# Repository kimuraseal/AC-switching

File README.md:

# 4CH AC, 2CH DC Switching and ZCD
The circuit consist of 
- Four optoisolated TRIAC switching circuit.
  Two channels being zero cross switched and other two being random phase switched.
- Two optoisolated MOSFET switching circuit.
  Capable of High speed operations.
- Zero Cross Detector.

# 4CH AC、2CH DC スイッチングおよびZCD
この回路は以下の構成になっています。
- 光アイソレーション付きTRIACスイッチング回路（4系統）
  2つはゼロクロススイッチング
  2つはランダムフェーズスイッチング
- 光アイソレーション付きMOSFETスイッチング回路（2系統）
  高速動作が可能
- ゼロクロス検出回路

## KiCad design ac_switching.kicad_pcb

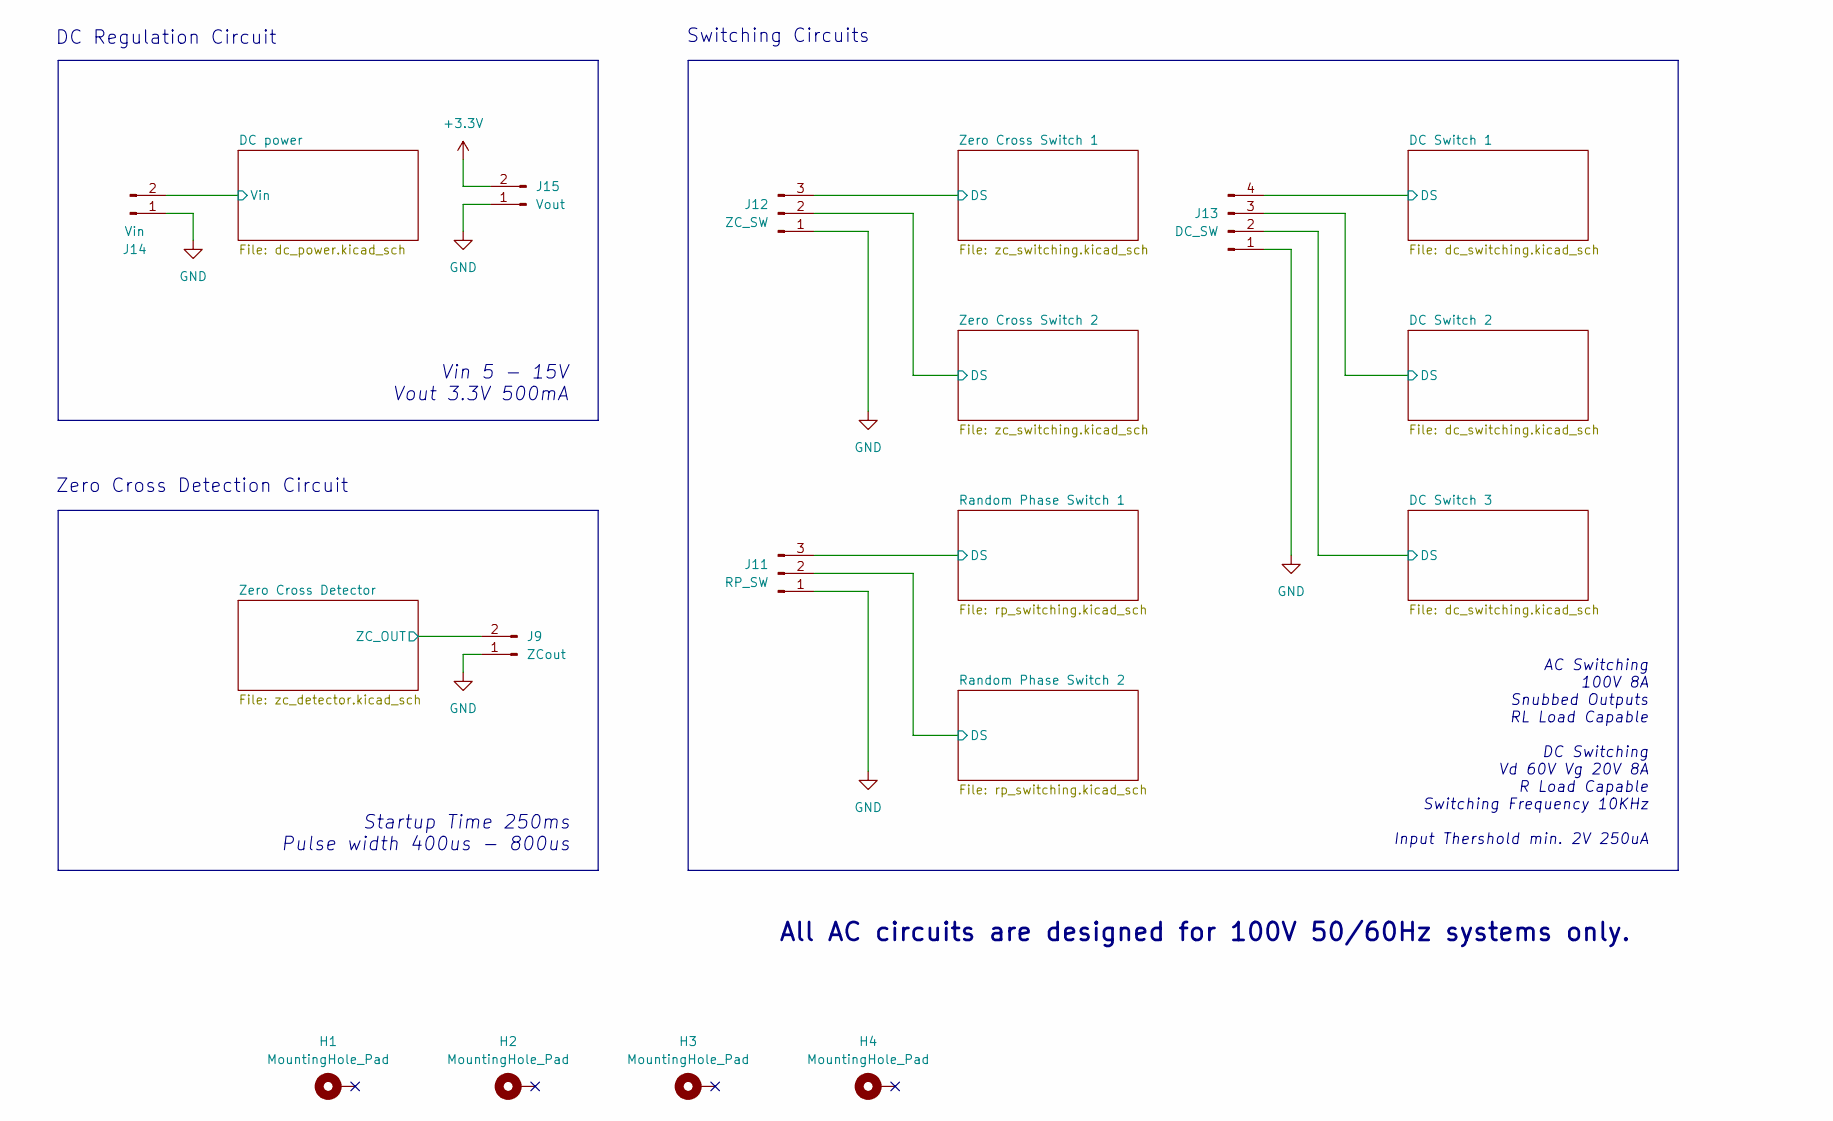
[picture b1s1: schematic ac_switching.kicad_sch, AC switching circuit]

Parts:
H1, H2, H3, H4: MountingHole_Pad; 3mm Mouting hole
J9: ZCout; PinSocket_1x02_P2.54mm_Vertical
J11: RP_SW; PinSocket_1x03_P2.54mm_Vertical
J12: ZC_SW; PinSocket_1x03_P2.54mm_Vertical
J13: DC_SW; PinSocket_1x04_P2.54mm_Vertical
J14: Vin; PinSocket_1x02_P2.54mm_Vertical
J15: Vout; PinSocket_1x02_P2.54mm_Vertical

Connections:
+3.3V: J15.2; also elsewhere on the board
/DC Switch 1/DS: J13.4; also elsewhere on the board
/DC Switch 2/DS: J13.3; also elsewhere on the board
/DC Switch 3/DS: J13.2; also elsewhere on the board
/DC power/Vin: J14.2; also elsewhere on the board
/Random Phase Switch 1/DS: J11.3; also elsewhere on the board
/Random Phase Switch 2/DS: J11.2; also elsewhere on the board
/Zero Cross Detector/ZC_OUT: J9.2; also elsewhere on the board
/Zero Cross Switch 1/DS: J12.3; also elsewhere on the board
/Zero Cross Switch 2/DS: J12.2; also elsewhere on the board
GND: J9.1, J11.1, J12.1, J13.1, J14.1, J15.1; also elsewhere on the board

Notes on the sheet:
Startup Time 250ms Pulse width 400us - 800us
Vin 5 - 15V Vout 3.3V 500mA
DC Regulation Circuit
AC Switching 100V 8A Snubbed Outputs RL Load Capable DC Switching Vd 60V Vg 20V 8A R Load Capable Switching Frequency 10KHz Input Thershold min. 2V 250uA
All AC circuits are designed for 100V 50/60Hz systems only.
Switching Circuits
Zero Cross Detection Circuit

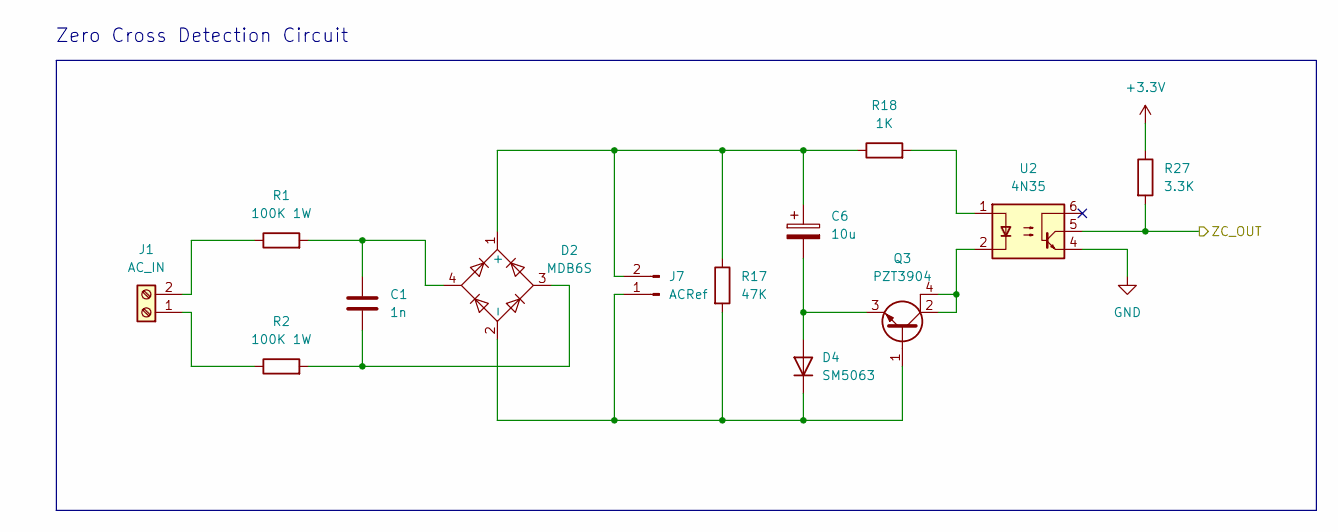
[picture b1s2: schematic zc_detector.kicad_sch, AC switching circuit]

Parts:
C1: 1n; TDK B32529C6102
C6: 10u; Rubycon YXF 50V 10uF
D2: MDB6S; TSSOP-4_4.4x5mm_P4mm
D4: SM5063; D_MELF
J1: AC_IN; TerminalBlock_bornier-2_P5.08mm
J7: ACRef; PinSocket_1x02_P2.54mm_Vertical
Q3: PZT3904; SOT-223
R1, R2: 100K 1W; Yageo RC_L 1218
R17: 47K; Yageo RC_L 1206
R18: 1K; Yageo RC_L 1206
R27: 3.3K; Yageo RC_L 1206
U2: 4N35; DIP-6_W7.62mm

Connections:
+3.3V: R27.1; also elsewhere on the board
/Zero Cross Detector/ZC_OUT: R27.2, U2.5; also elsewhere on the board
GND: U2.4; also elsewhere on the board
unnamed: C1.1, D2.4, R1.2
unnamed: C1.2, D2.3, R2.2
unnamed: C6.1, D2.1 (+), J7.2, R17.1, R18.1
unnamed: D2.2 (-), D4.1 (K), J7.1, Q3.1 (B), R17.2
unnamed: C6.2, D4.2 (A), Q3.3 (E)
unnamed: J1.1, R2.1
unnamed: J1.2, R1.1
unnamed: Q3.2 (C), Q3.4 (C), U2.2
unnamed: R18.2, U2.1

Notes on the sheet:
Zero Cross Detection Circuit

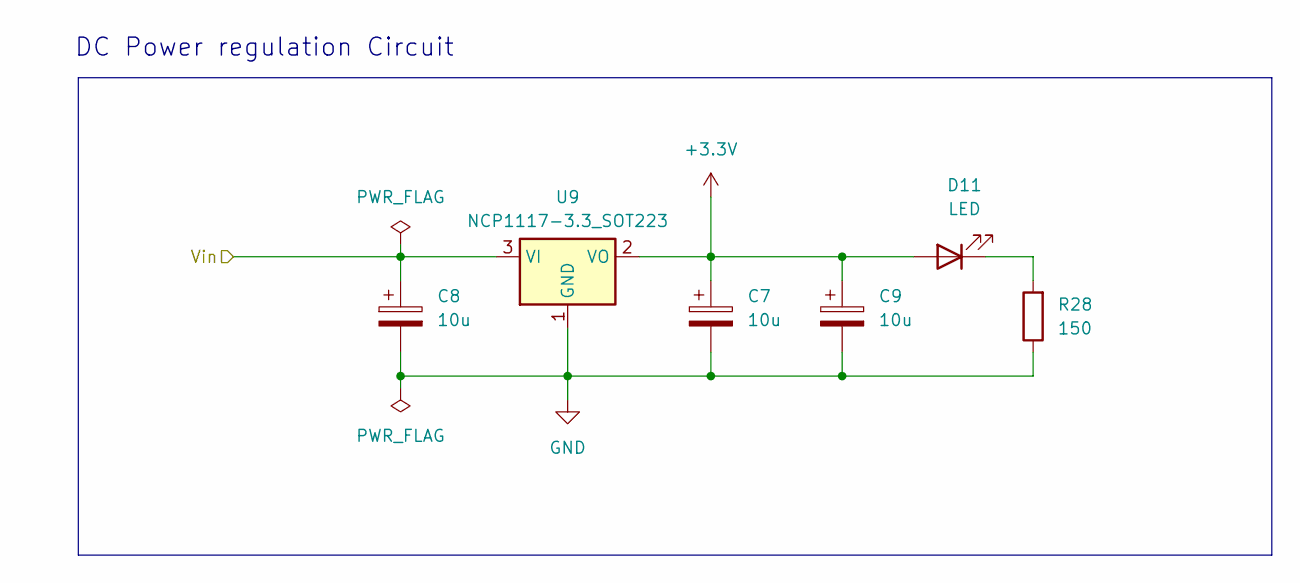
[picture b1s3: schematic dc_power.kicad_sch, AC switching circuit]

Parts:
C7, C8, C9: 10u; Rubycon YXF 50V 10uF
D11: LED; Lite On LTST-C150
R28: 150; Yageo RC_L 1206
U9: NCP1117-3.3_SOT223; SOT-223-3_TabPin2

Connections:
+3.3V: C7.1, C9.1, D11.2 (A), U9.2 (VO); also elsewhere on the board
/DC power/Vin: C8.1, U9.3 (VI); also elsewhere on the board
GND: C7.2, C8.2, C9.2, R28.1, U9.1 (GND); also elsewhere on the board
unnamed: D11.1 (K), R28.2

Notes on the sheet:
DC Power regulation Circuit

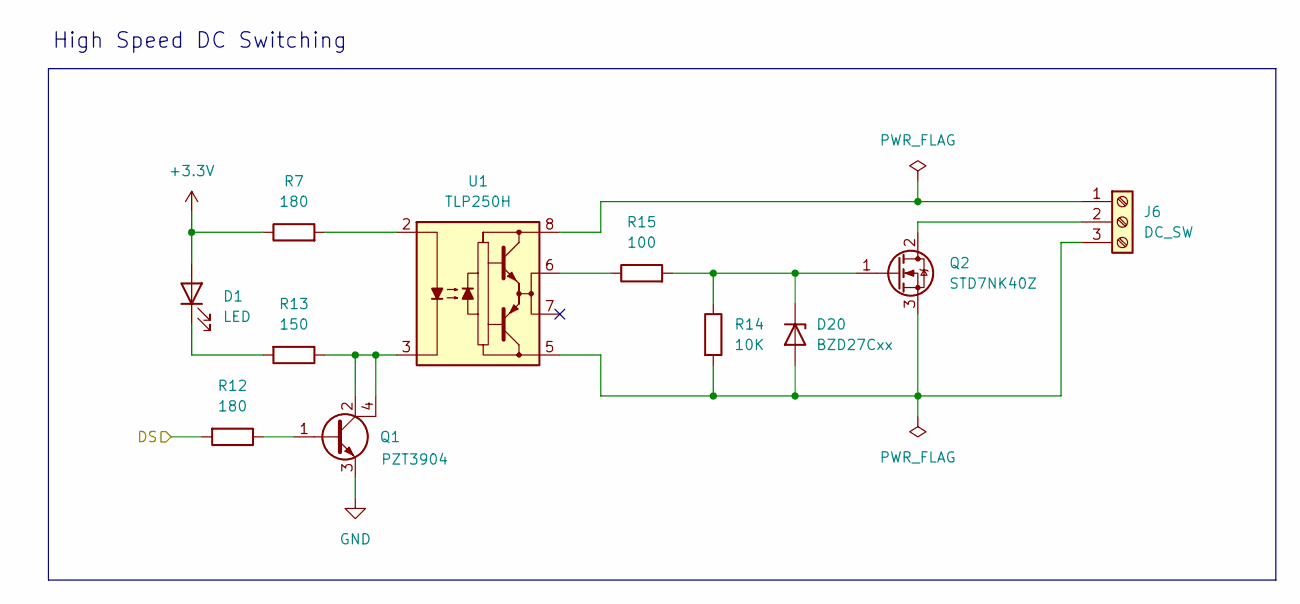
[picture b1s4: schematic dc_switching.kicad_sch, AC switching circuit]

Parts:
D1: LED; Lite On LTST-C150
D20: BZD27Cxx; D_SMF
J6: DC_SW; TerminalBlock_bornier-3_P5.08mm
Q1: PZT3904; SOT-223
Q2: STD7NK40Z; TO-252-2
R7, R12: 180; Yageo RC_L 1206
R13: 150; Yageo RC_L 1206
R14: 10K; Yageo RC_L 1206
R15: 100; Yageo RC_L 1206
U1: TLP250H; DIP-8_W7.62mm

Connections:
+3.3V: D1.2 (A), R7.1; also elsewhere on the board
/DC Switch 1/DS: R12.2; also elsewhere on the board
GND: Q1.3 (E); also elsewhere on the board
unnamed: D1.1 (K), R13.2
unnamed: D20.2 (A), J6.3, Q2.3 (S), R14.2, U1.5 (VEE)
unnamed: D20.1 (K), Q2.1 (G), R14.1, R15.2
unnamed: J6.1, U1.8 (VCC)
unnamed: J6.2, Q2.2 (D)
unnamed: Q1.1 (B), R12.1
unnamed: R15.1, U1.6 (VO)
unnamed: R7.2, U1.2 (A)
unnamed: Q1.2 (C), Q1.4 (C), R13.1, U1.3 (C)

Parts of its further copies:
D8, D16: LED; Lite On LTST-C150
D21, D22: BZD27Cxx; D_SMF
J8, J10: DC_SW; TerminalBlock_bornier-3_P5.08mm
Q4, Q10: PZT3904; SOT-223
Q5, Q11: STD7NK40Z; TO-252-2
R16, R23, R41, R45: 180; Yageo RC_L 1206
R24, R42: 150; Yageo RC_L 1206
R25, R44: 100; Yageo RC_L 1206
R26, R43: 10K; Yageo RC_L 1206
U3, U8: TLP250H; DIP-8_W7.62mm

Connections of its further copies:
+3.3V: D8.2 (A), D16.2 (A), R16.1, R45.1; also elsewhere on the board
/DC Switch 2/DS: R23.2; also elsewhere on the board
/DC Switch 3/DS: R41.2; also elsewhere on the board
GND: Q4.3 (E), Q10.3 (E); also elsewhere on the board
unnamed: D8.1 (K), R24.2
unnamed: D16.1 (K), R42.2
unnamed: D21.2 (A), J8.3, Q5.3 (S), R26.2, U3.5 (VEE)
unnamed: D21.1 (K), Q5.1 (G), R25.2, R26.1
unnamed: D22.2 (A), J10.3, Q11.3 (S), R43.2, U8.5 (VEE)
unnamed: D22.1 (K), Q11.1 (G), R43.1, R44.2
unnamed: J8.1, U3.8 (VCC)
unnamed: J8.2, Q5.2 (D)
unnamed: J10.1, U8.8 (VCC)
unnamed: J10.2, Q11.2 (D)
unnamed: Q4.1 (B), R23.1
unnamed: Q10.1 (B), R41.1
unnamed: R25.1, U3.6 (VO)
unnamed: R44.1, U8.6 (VO)
unnamed: R16.2, U3.2 (A)
unnamed: Q4.2 (C), Q4.4 (C), R24.1, U3.3 (C)
unnamed: R45.2, U8.2 (A)
unnamed: Q10.2 (C), Q10.4 (C), R42.1, U8.3 (C)

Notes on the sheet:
High Speed DC Switching

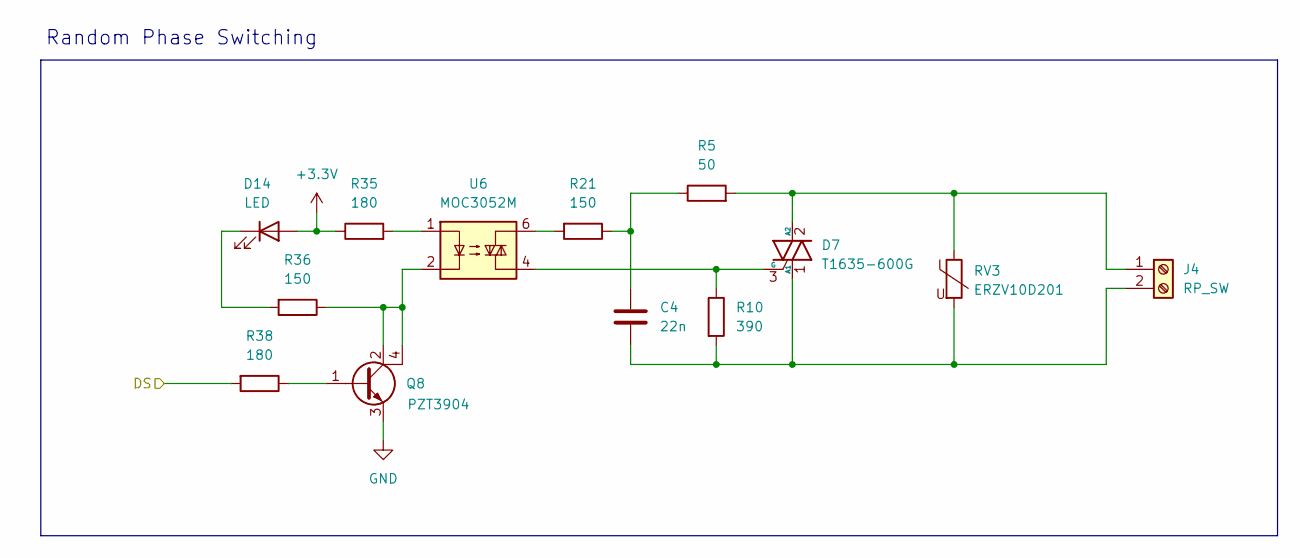
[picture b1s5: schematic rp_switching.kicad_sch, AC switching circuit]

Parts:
C4: 22n; TDK B32682A4223
D7: T1635-600G; ST MIcroelectronics T16xx
D14: LED; Lite On LTST-C150
J4: RP_SW; TerminalBlock_bornier-2_P5.08mm
Q8: PZT3904; SOT-223
R5: 50; Yageo RC_L 1218
R10: 390; Yageo RC_L 1206
R21, R36: 150; Yageo RC_L 1206
R35, R38: 180; Yageo RC_L 1206
RV3: ERZV10D201; Panasonic ERZV10D201
U6: MOC3052M; DIP-6_W7.62mm

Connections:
+3.3V: D14.2 (A), R35.1; also elsewhere on the board
/Random Phase Switch 1/DS: R38.2; also elsewhere on the board
GND: Q8.3 (E); also elsewhere on the board
unnamed: C4.1, R5.1, R21.1
unnamed: C4.2, D7.1 (A1), J4.2, R10.2, RV3.2
unnamed: D7.2 (A2), J4.1, R5.2, RV3.1
unnamed: D7.3 (G), R10.1, U6.4
unnamed: D14.1 (K), R36.2
unnamed: Q8.1 (B), R38.1
unnamed: Q8.2 (C), Q8.4 (C), R36.1, U6.2
unnamed: R21.2, U6.6
unnamed: R35.2, U6.1

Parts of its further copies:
C5: 22n; TDK B32682A4223
D9: T1635-600G; ST MIcroelectronics T16xx
D15: LED; Lite On LTST-C150
J5: RP_SW; TerminalBlock_bornier-2_P5.08mm
Q9: PZT3904; SOT-223
R6: 50; Yageo RC_L 1218
R11: 390; Yageo RC_L 1206
R22, R39: 150; Yageo RC_L 1206
R37, R40: 180; Yageo RC_L 1206
RV4: ERZV10D201; Panasonic ERZV10D201
U7: MOC3052M; DIP-6_W7.62mm

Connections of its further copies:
+3.3V: D15.2 (A), R37.1; also elsewhere on the board
/Random Phase Switch 2/DS: R40.2; also elsewhere on the board
GND: Q9.3 (E); also elsewhere on the board
unnamed: C5.1, R6.1, R22.1
unnamed: C5.2, D9.1 (A1), J5.2, R11.2, RV4.2
unnamed: D9.2 (A2), J5.1, R6.2, RV4.1
unnamed: D9.3 (G), R11.1, U7.4
unnamed: D15.1 (K), R39.2
unnamed: Q9.1 (B), R40.1
unnamed: Q9.2 (C), Q9.4 (C), R39.1, U7.2
unnamed: R22.2, U7.6
unnamed: R37.2, U7.1

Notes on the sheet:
Random Phase Switching

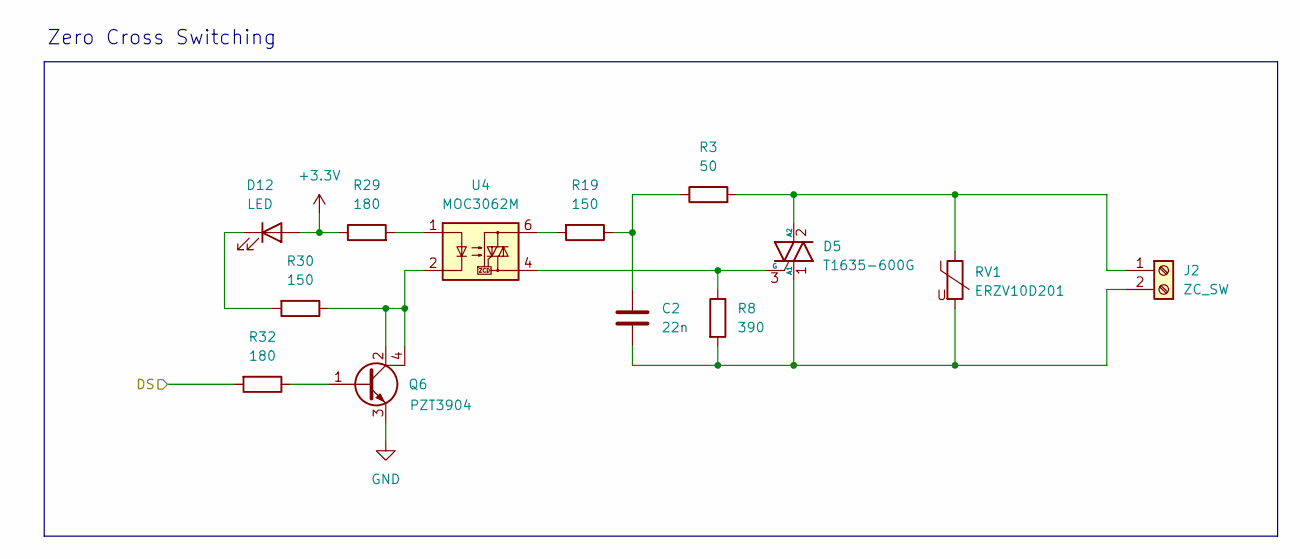
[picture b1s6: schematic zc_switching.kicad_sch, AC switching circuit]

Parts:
C2: 22n; TDK B32682A4223
D5: T1635-600G; ST MIcroelectronics T16xx
D12: LED; Lite On LTST-C150
J2: ZC_SW; TerminalBlock_bornier-2_P5.08mm
Q6: PZT3904; SOT-223
R3: 50; Yageo RC_L 1218
R8: 390; Yageo RC_L 1206
R19, R30: 150; Yageo RC_L 1206
R29, R32: 180; Yageo RC_L 1206
RV1: ERZV10D201; Panasonic ERZV10D201
U4: MOC3062M; DIP-6_W7.62mm

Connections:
+3.3V: D12.2 (A), R29.1; also elsewhere on the board
/Zero Cross Switch 1/DS: R32.2; also elsewhere on the board
GND: Q6.3 (E); also elsewhere on the board
unnamed: C2.1, R3.1, R19.1
unnamed: C2.2, D5.1 (A1), J2.2, R8.2, RV1.2
unnamed: D5.2 (A2), J2.1, R3.2, RV1.1
unnamed: D5.3 (G), R8.1, U4.4
unnamed: D12.1 (K), R30.2
unnamed: Q6.1 (B), R32.1
unnamed: Q6.2 (C), Q6.4 (C), R30.1, U4.2
unnamed: R19.2, U4.6
unnamed: R29.2, U4.1

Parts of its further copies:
C3: 22n; TDK B32682A4223
D6: T1635-600G; ST MIcroelectronics T16xx
D13: LED; Lite On LTST-C150
J3: ZC_SW; TerminalBlock_bornier-2_P5.08mm
Q7: PZT3904; SOT-223
R4: 50; Yageo RC_L 1218
R9: 390; Yageo RC_L 1206
R20, R31: 150; Yageo RC_L 1206
R33, R34: 180; Yageo RC_L 1206
RV2: ERZV10D201; Panasonic ERZV10D201
U5: MOC3062M; DIP-6_W7.62mm

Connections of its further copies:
+3.3V: D13.2 (A), R33.1; also elsewhere on the board
/Zero Cross Switch 2/DS: R34.2; also elsewhere on the board
GND: Q7.3 (E); also elsewhere on the board
unnamed: C3.1, R4.1, R20.1
unnamed: C3.2, D6.1 (A1), J3.2, R9.2, RV2.2
unnamed: D6.2 (A2), J3.1, R4.2, RV2.1
unnamed: D6.3 (G), R9.1, U5.4
unnamed: D13.1 (K), R31.2
unnamed: Q7.1 (B), R34.1
unnamed: Q7.2 (C), Q7.4 (C), R31.1, U5.2
unnamed: R20.2, U5.6
unnamed: R33.2, U5.1

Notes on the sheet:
Zero Cross Switching

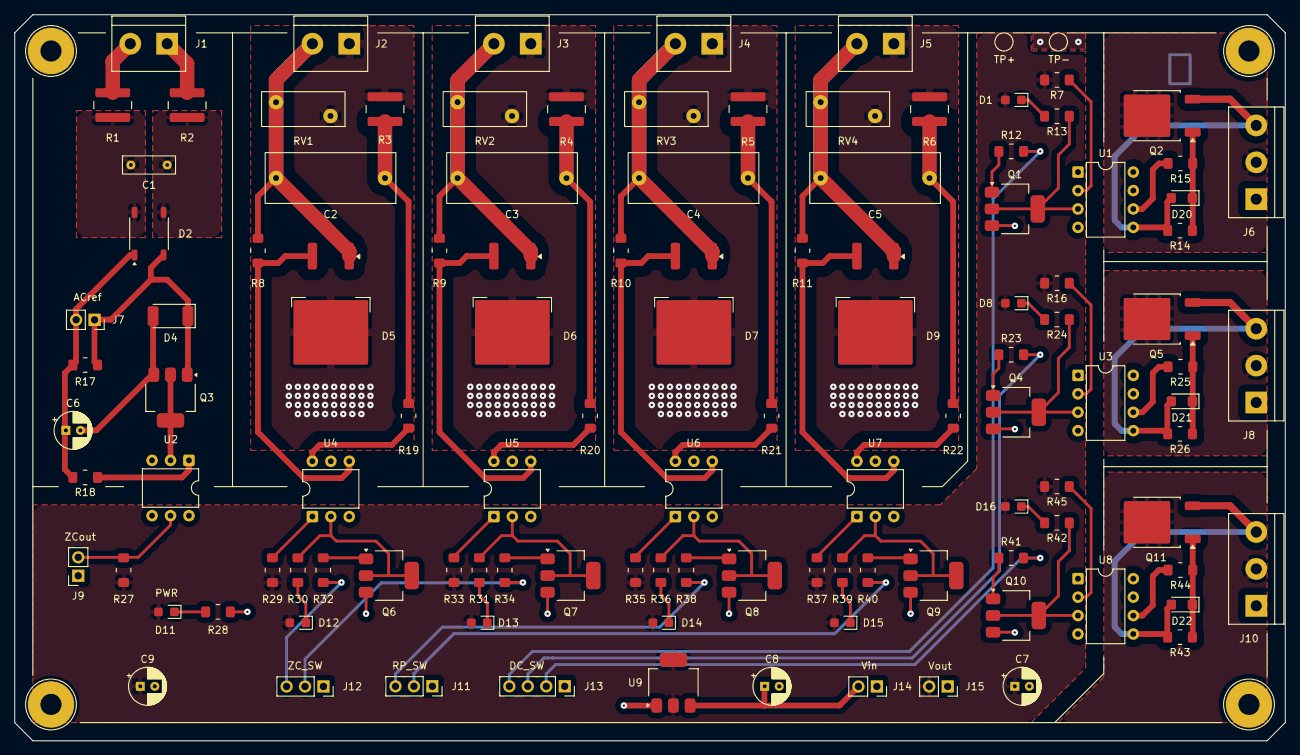
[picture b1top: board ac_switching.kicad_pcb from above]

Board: 2 copper layers, 175.0 x 100.0 mm, 114 parts (0 on the bottom side), 84 nets.

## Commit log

2025-03-12 initial circuit schematic with sources
2025-03-13 footprint work started
2025-03-14 updated to pcb and footprints
2025-03-17 footprint attached and 2 channels done
2025-03-17 PCB completed
2025-03-18 PCB complete
2025-03-18 changes
    varistor replacement, cleaning up the layout and traces
2025-03-18 Circuit Schematic updated
2025-03-19 increased the trace width and trace clearance.
2025-03-19 Production ready
2025-03-21 minor PCB fix
2025-03-21 GERBER updated
2025-03-21 Merged zero crossing circuit
2025-03-24 Compartmentalization
2025-03-26 DC Switching Schematic complete
2025-03-27 PCB updates
2025-03-27 pcb progress
2025-03-28 PCB progress
2025-03-31 Data Sheet added
    PCB complete, Final Footprint checks are pending
2025-03-31 some minor changes to the PCB after DFM
2025-03-31 Production Version
2025-04-01 BOM added
2025-04-01 Schematic Update
2025-04-01 BOM update
